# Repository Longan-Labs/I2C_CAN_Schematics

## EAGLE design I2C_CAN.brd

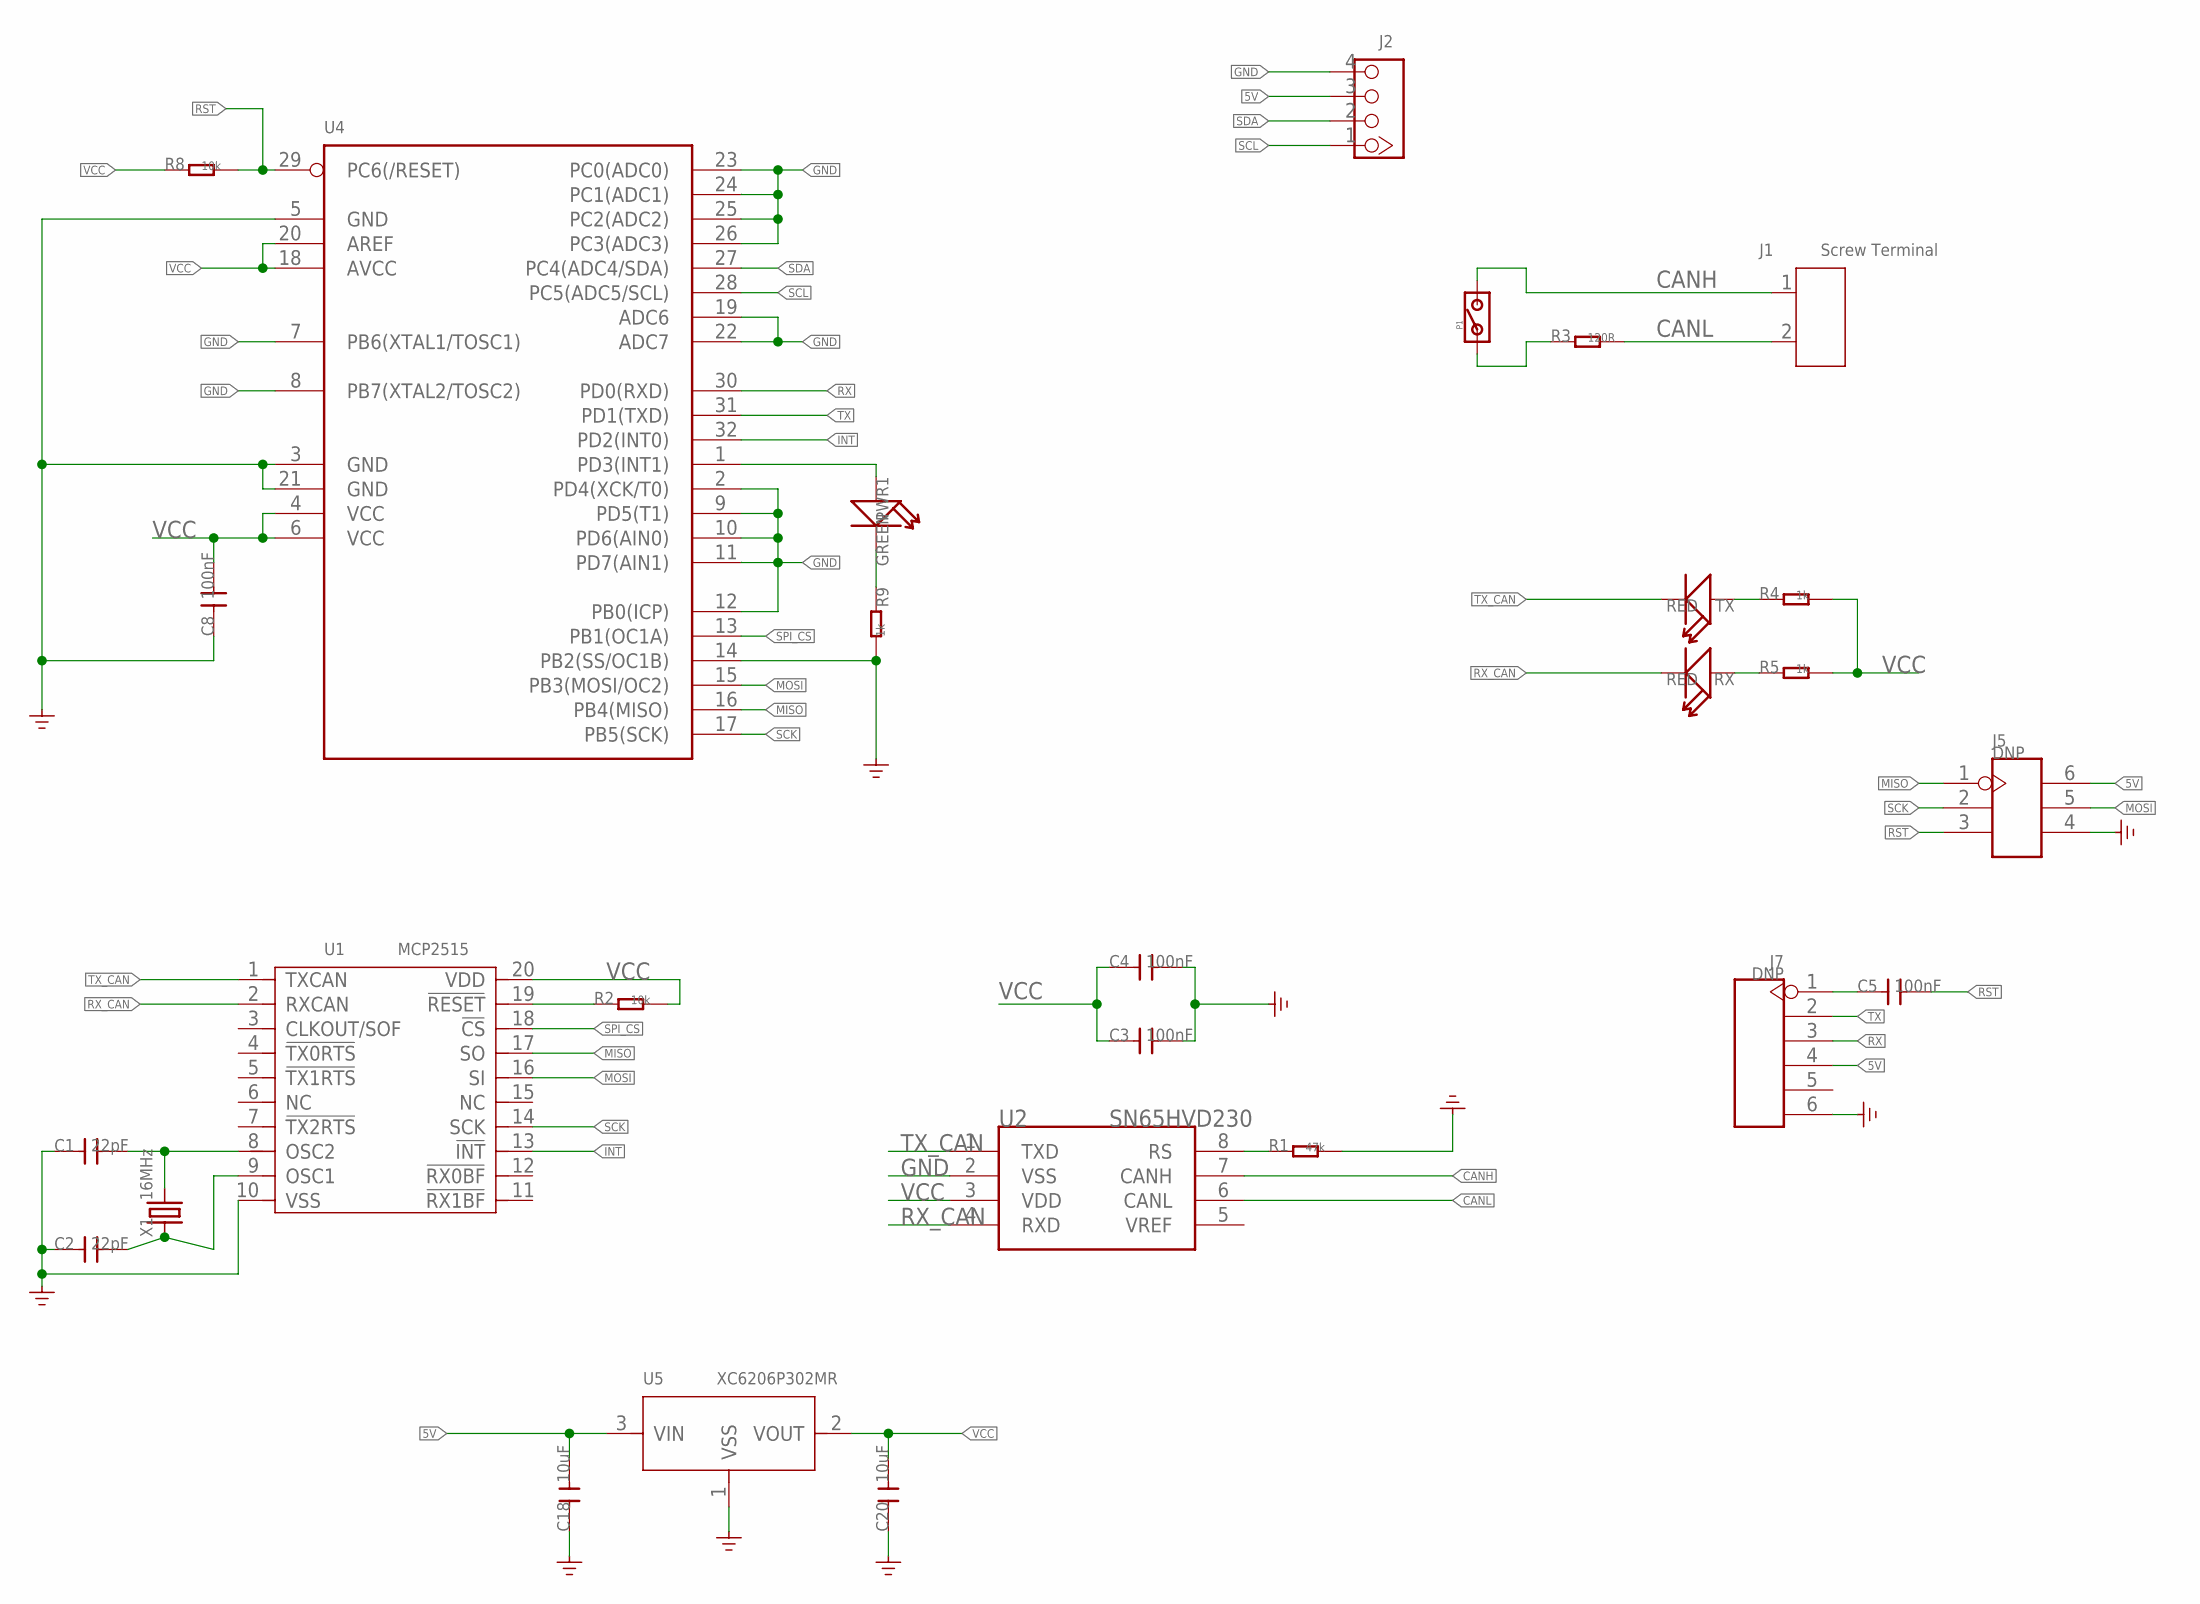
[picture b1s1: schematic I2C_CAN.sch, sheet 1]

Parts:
C1, C2: 22pF; 0603
C3, C4, C5, C8: 100nF; 0603
C18, C20: 10uF; C0603
J1: Screw Terminal; 2P-3.5
J2: 320110033; HW4-2.0
J5: DNP; H2X3-SMD-2.0(1.143)
J7: DNP; H6-2.54
P1: PAD-JUMPER-2P; 2P-SMD-1.78X1.27
PWR1: GREEN; LED-0603
R1: 47k; 0603
R2, R8: 10k; 0603
R3: 120R; 0603
R4, R5, R9: 1k; 0603
RX: RED; LED-0603
TX: RED; LED-0603
U1: MCP2515; TSSOP20-0.65-6.5X4.4MM
U2: SN65HVD230; SOIC8-6.0
U4: MCU-ATMEGA8/168/328'AU'; TQFP32-0.8-7X7MM
U5: XC6206P302MR; SOT-23
X1: 16MHz; HC49US

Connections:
5V: C18.2, J2.3, J5.6, J7.4, U5.3 (VIN)
CANH: J1.1, P1.2, U2.7 (CANH)
CANL: J1.2, R3.2, U2.6 (CANL)
GND: C1.1, C2.1, C3.2, C4.2, C8.1, C18.1, C20.1, J2.4, J5.4, J7.6, R1.2, R9.2, U1.10 (VSS), U2.2 (VSS), U4.2 (PD4(XCK/T0)), U4.3 (GND), U4.5 (GND), U4.7 (PB6(XTAL1/TOSC1)), U4.8 (PB7(XTAL2/TOSC2)), U4.9 (PD5(T1)), U4.10 (PD6(AIN0)), U4.11 (PD7(AIN1)), U4.12 (PB0(ICP)), U4.14 (PB2(SS/OC1B)), U4.19 (ADC6), U4.21 (GND), U4.22 (ADC7), U4.23 (PC0(ADC0)), U4.24 (PC1(ADC1)), U4.25 (PC2(ADC2)), U4.26 (PC3(ADC3)), U5.1 (VSS)
INT: U1.13 (!INT), U4.32 (PD2(INT0))
MISO: J5.1, U1.17 (SO), U4.16 (PB4(MISO))
MOSI: J5.5, U1.16 (SI), U4.15 (PB3(MOSI/OC2))
unnamed: P1.1, R3.1
unnamed: R4.1, TX.+
unnamed: C5.1, J7.1
unnamed: PWR1.+, U4.1 (PD3(INT1))
unnamed: PWR1.-, R9.1
unnamed: R5.1, RX.+
unnamed: C1.2, U1.8 (OSC2), X1.2
unnamed: C2.2, U1.9 (OSC1), X1.1
unnamed: R1.1, U2.8 (RS)
RST: C5.2, J5.3, R8.2, U4.29 (PC6(/RESET))
RST_N: R2.1, U1.19 (!RESET)
RX: J7.3, U4.30 (PD0(RXD))
RX_CAN: RX.-, U1.2 (RXCAN), U2.4 (RXD)
SCK: J5.2, U1.14 (SCK), U4.17 (PB5(SCK))
SCL: J2.1, U4.28 (PC5(ADC5/SCL))
SDA: J2.2, U4.27 (PC4(ADC4/SDA))
SPI_CS: U1.18 (!CS), U4.13 (PB1(OC1A))
TX: J7.2, U4.31 (PD1(TXD))
TX_CAN: TX.-, U1.1 (TXCAN), U2.1 (TXD)
VCC: C3.1, C4.1, C8.2, C20.2, R2.2, R4.2, R5.2, R8.1, U1.20 (VDD), U2.3 (VDD), U4.4 (VCC), U4.6 (VCC), U4.18 (AVCC), U4.20 (AREF), U5.2 (VOUT)

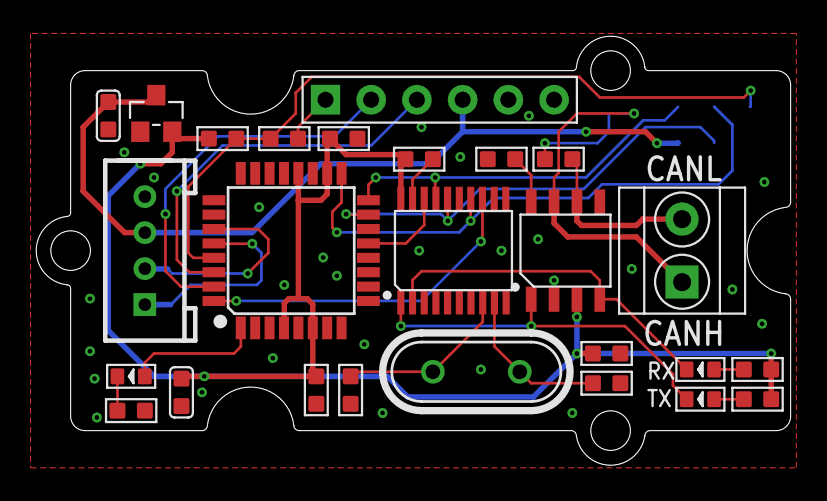
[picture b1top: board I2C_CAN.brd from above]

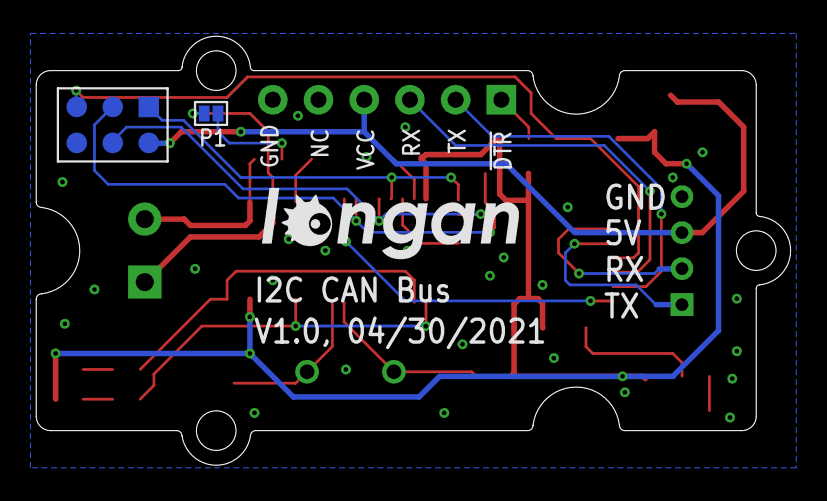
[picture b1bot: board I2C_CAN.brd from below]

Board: 2 copper layers, 41.9 x 23.8 mm, 30 parts (3 on the bottom side), 27 nets.

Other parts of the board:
U3: GROVE-TEST-PLATFORM
U$5: LONGAN-SILK-SMALLER

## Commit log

2021-05-14 first push
